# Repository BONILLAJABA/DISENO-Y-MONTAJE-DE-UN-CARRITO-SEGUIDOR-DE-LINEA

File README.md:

# DISENO-Y-MONTAJE-DE-UN-CARRITO-SEGUIDOR-DE-LINEA

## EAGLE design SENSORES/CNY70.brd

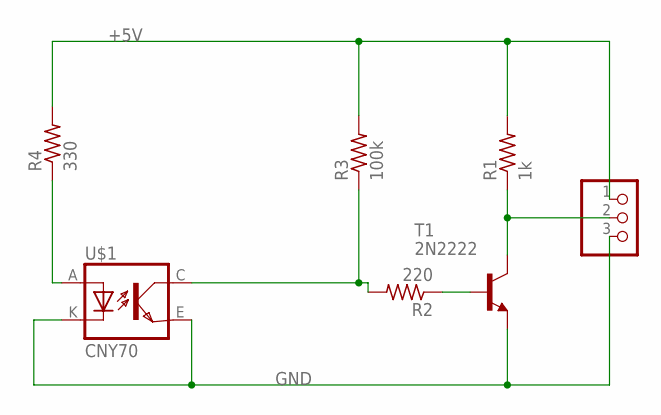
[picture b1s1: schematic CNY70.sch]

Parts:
JP1: PINHD-1X3; 1X03
R1: 1k; 0207/10
R2: 220; 0207/10
R3: 100k; 0207/10
R4: 330; 0207/10
T1: 2N2222; TO92-EBC-OVAL
U$1: CNY70; 4

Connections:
+5V: JP1.1, R1.2, R3.2, R4.2
GND: JP1.3, T1.E, U$1.E (EMI), U$1.K (C)
unnamed: R2.2, R3.1, U$1.C (COL)
unnamed: R2.1, T1.B
unnamed: R4.1, U$1.A
unnamed: JP1.2, R1.1, T1.C

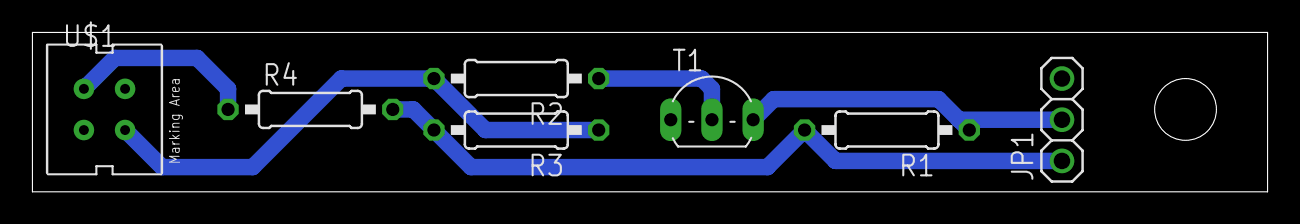
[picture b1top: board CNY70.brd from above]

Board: 2 copper layers, 76.2 x 9.8 mm, 7 parts (0 on the bottom side), 6 nets.
